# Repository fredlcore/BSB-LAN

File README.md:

# BSB-LPB-PPS-LAN

Die deutsche Fassung dieser Datei gibt es [hier](README_de.md).

Before getting started, please read through the manual [here](https://docs.bsb-lan.de).

BSB-LAN is a software/hardware solution for accessing the “Boiler-System-Bus” (BSB), the “Local-Process-Bus (LPB)” and the “Punkt-zu-Punkt-Schnittstelle” (PPS). The adapter is available for various *ESP32*-based microcontrollers (ESP32 NodeMCU, Olimex EVB, Olimex POE-ISO) as well as for an *Arduino Due* with Ethernet shield. It allows accessing the heating systems from Atlantic, Brötje, Elco and many other manufacturers via LAN/WLAN, provided that they use one of the Siemens controllers listed below. BSB-LAN makes it possible to control or regulate the heating and log any given values. This project supports almost all parameters available on the heating systems and can be used for in a comprehensive home automation environment.  

---

***Interface kits available!***  
**Interface boards are available for the ESP32 upon request. These can simply be plugged on top of one of the listed microcontrollers.Getting the board from here helps supporting this project in the future, so if you are interested, please send Frederik an e-mail (German or English) to <br /> bsb (ät) code-it.de <br /> for further information.**  

---  

Using the adapter and the BSB-LAN software, various values and parameters can easily be monitored, logged and, if so desired, controlled and changed via a web-interface.
Optional integration into existing smart home systems such as FHEM, openHAB, HomeMatic, ioBroker, Loxone, IP-Symcon, EDOMI, Home Assistant, SmartHomeNG or Node-RED is possible via MQTT, JSON or HTTP access. 
The adapter can also be used as a standalone logger without LAN or Internet connection when using a microSD card (MBR partition / FAT format).  
Temperature and humidity sensors can also be connected and their data can also be logged and analyzed. The option of integrating your own code into the BSB-LAN software also offers a wide range of expansion options. 
        
**In the following, some model series from different manufacturers are listed, which usually have installed BSB-LAN compatible controllers:**  
- Brötje: BBK, BBS, BGB, BLW (**see exceptions below!**), BMK, BMR, BOB, BSK, BSW, Eurocontrol, ISR, LogoBloc, SGB, SOB, SPK, WBC (**see exceptions below!**), WBS (**see exceptions below!**), WGB (**see exceptions below!**), WMC, WMS, WOB
- **Not working Brötje models: BOK, BLW Eco, BLW Eco.2, BLW Mono, BLW Mono.1, BLW Neo, BLW Pro.1, BLW Split, BSW Neo, WBC 22.1/28.1, WBC 14.1/22.1, WGB-K 22.1/28.1, WGB 14.1/22.1/28.1/38.1, WHB, WHC, WHS, WLC, WLS and all others with IWR controller**  
- Bösch: heat pumps with RVS controller type
- Elco: Aerotop (**not EVO LN / Mono / Mono.2 / Split / Split.2!**), Aquatop, Rendamax, Straton, Thision (**not Thision Mini!**), Thision S, Thision S Plus, Trigon S Plus
- Alarko: Aldens WM/WS
- ATAG: QR
- Atlantic: Axeo, Alféa Excellia A.I., Alféa Extensa A.I., Hynea hybrid duo gaz, Navistem, Perfinox, Varmax
- Austria Email: LWP, LWPK
- Baxi: Luna Platinum, Luna Duo, Block Kondens
- Boesch: SLS
- Bosch: Condens 3500 F, Condens 7500 FM
- Chappée: Luna, Klista
- CitrinSolar: proClima
- CTA: Optiheat
- CTC: 380 IC
- De Dietrich: IX 145
- Deville: 9942, 9981
- District heating: RVD230
- Eco: AiWA, AW, BW, DW, heatLite, Star, TBW, WW, WWi, TWW
- Ecostar: Ecodense WT-S 45
- Etna: II GWS
- EVI Heat: Combi-7
- Ferroli: HMP
- Froeling: Rendagas Plus
- Fujitsu Waterstage: Comfort, Duo, WOHA, WSHA, WSYA, WSYK, WSYP
- Gebwell: T2
- Geminox: Thrs
- General: (aka Fujitsu Waterstage) WC13F / WOC13RIYF / WGHA 100DG
- Gorenje: Aerogor Compact, Aerogor Compact EVI, Aerogor ECO Inverter 10 A, Aerogor Split AW, Aerogor Split HD, Aerogor Split HD EVI, Aquagor, Aquagor EVI, Geogor All-In-One, Terragor, Terragor EVI
- Grünenwald: Greenheat
- GS: UnoTec
- Hansa: SND
- Herz: Commotherm 5 DeLuxe
- Hotjet: One2, Wx, ZETXe, ZETXi
- Ideal Heating: Halo Air, Logic Air Heat Pump
- Interdomo: Domostar GBK 25H/SH, OBK (HC 232)
- MAN/MHG: Ecostar 200
- MHG: EcoSmart ES, EcoStar 500, EcoStar 750, ecoWP Xe, Procon E, Procon GWB, Procon HT
- Müba: Ultra Clean Eco
- Oilon: CUBE House, GT, SH, SHx
- Olymp: RegelStar 3000, SHS, WHS
- Palazzetti: Choro Sistema Calore
- Potterton: Paramount
- Robur: Comfort Controller, K18 Simplygas / Hybrigas
- Sieger: TG11
- Šildymo Technologijų Centras (ŠTC): STC9
- Sixmadun: TG11BE
- Smartheat: UI400
- SSP: Proburner
- Strebel: S-ASX
- Sunex: Nexus
- Termomax: Termo ÖV
- Thercon: Therma Silent Coax Single, THERMA Silent Coax Combi 300/500
- Thermics: Energie
- Thermital: TBox Clima TOP
- Tifell: Biofell
- Variheat: 110C
- Viadrus : Claudius K1, K2
- Viessmann: Vitotwin 300-W (exclusively!)
- Wamak: AiWa, DB
- Weishaupt: WTU  

If your heater has one of the following controllers, but your model is not listed in our manual, feel free to get in touch with us, as these models have been confirmed working:  
AVS37, AVS55, AVS71, AVS74, AVS75, AVS77, AVS79, LMS14, LMS15, LMS15, LMU64, LMU74, LMU75, RVA61, RVA63, RVA33, RVA36, RVA43, RVA46, RVA47, RVA53, RVA60, RVA61, RVA63, RVA65, RVA66, RVC32, RVD110, RVD115, RVD120, RVD125, RVD130, RVD135, RVD139, RVD140, RVD144, RVD145, RVD230, RVD235, RVD240, RVD245, RVD250, RVD255, RVD260, RVD265, RVL469, RVL470, RVL471, RVL472, RVL479, RVL480, RVL481, RVL482, RVP320, RVP330, RVP340, RVP350, RVP351, RVP360, RVP361, RVP5xx, RVS13, RVS21, RVS23, RVS26, RVS41, RVS43, RVS46, RVS47, RVS51, RVS53, RVS61, RVS63, RVS65, RVS68, RWI65, WRI80
<BR><BR>

<B>Attention!</B><BR>
Some companies which previously used BSB/LPB in their heating systems have now switched to other systems for their lower-cost devices. Examples are Brötje's WLC/WLS/BOK series. These are not compatible with BSB/LPB and only allow very limited parameters to be configured by the user. If you have one of these heating systems, you are so far out of luck to configure and monitor your heating system as it can be done with the more expensive (but BSB/LPB compatible) devices mentioned above among others.
In addition, there are now also Siemens controllers that no longer expose BSB/LPB connectors, but use different bus systems, for example the LMU34 and the Climatix/POS-series.
<BR><BR>
Instructions on how to configure etc. can be found in the <A HREF="https://docs.bsb-lan.de">manual</A>.<BR>
The forum thread that led to the development of this interface can be found <A HREF="http://forum.fhem.de/index.php?topic=29762.new;topicseen#new">here</A>.<BR>
(Forum is in German, but several members speak English)

Please take note that while the board can also be used on the Raspberry Pi, the software provided here only runs on the ESP32 and Arduino Due respectively! For using the board with the Pi, you have to use the software bsb_gateway which is available <A HREF="https://github.com/loehnertj/bsbgateway">here</A>. Please also note that the functionality differs significantly, and that you would have to contact the author of bsb_gateway for any question related to it.

Web-Interface screenshots:

BSB-Board populated for ESP32 Olimex boards:

BSB-Board on Olimex POE inside the project's 3D-printed case:

<br />This work is licensed under a <a rel="license" href="http://creativecommons.org/licenses/by-nc-sa/4.0/">Creative Commons Attribution-NonCommercial-ShareAlike 4.0 International License</a>.

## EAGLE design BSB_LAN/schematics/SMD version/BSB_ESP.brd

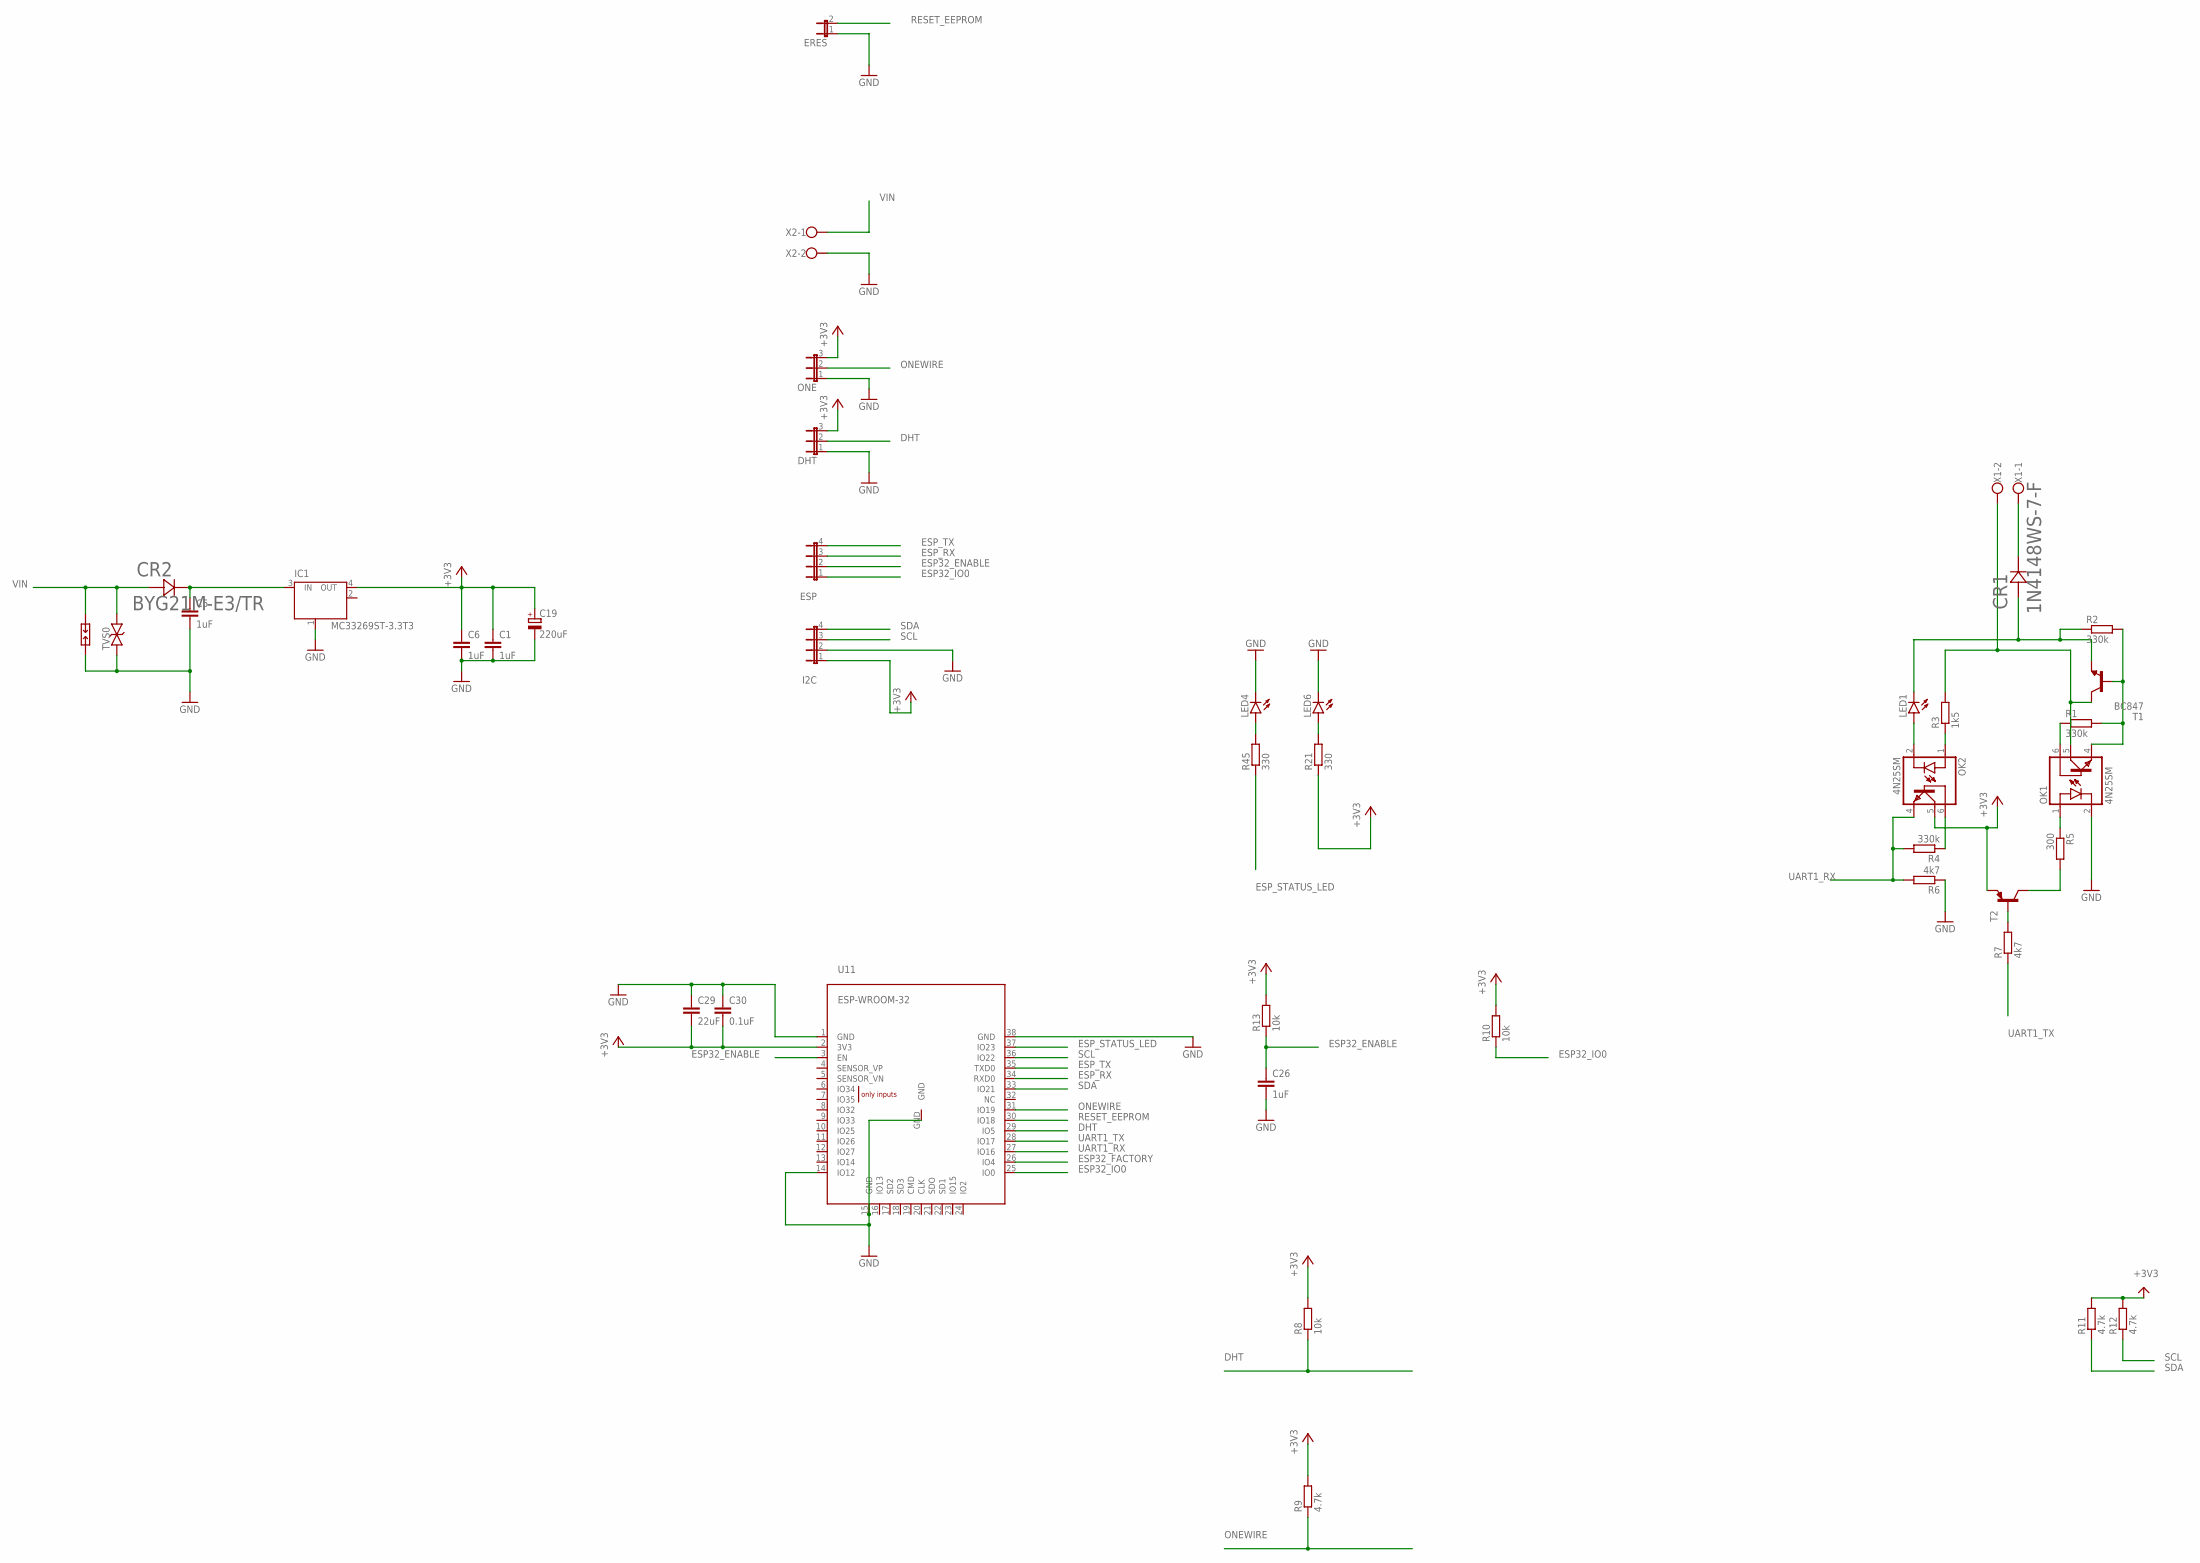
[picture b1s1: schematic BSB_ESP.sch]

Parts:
C1: 1uF; C1210
C5, C6: 1uF; C0805
C19: 220uF; 153CLV-0807
C26: 1uF; C0603
C29: 22uF; C0805
C30: 0.1uF; C0805
CR1: 1N4148WS-7-F; SOD323_DIO
CR2: BYG21M-E3/TR; DO-214AC_VIS
DHT: JP2E; JP2
ERES: JP1E; JP1
ESP: JP4E; JP4
I2C: JP4E; JP4
IC1: MC33269ST-3.3T3; SOT223
LED1, LED4, LED6: LEDCHIP-LED0805; CHIP-LED0805
OK1, OK2: 4N25SM; DIL6-SMD
ONE: JP2E; JP2
R1, R2, R4: 330k; R0603
R3: 1k5; R0603
R5: 300; R0603
R6, R7: 4k7; R0603
R8: 10k; R0402
R9: 4.7k; R0402
R10, R13: 10k; R0603
R11, R12: 4.7k; R0603
R21, R45: 330; R0603
SP0: PCB-SGAP
T1: BC847; SOT23
T2: BC857A-PNP-SOT23-BEC; SOT23-BEC
TVS0: 43CA; SMB
U11: ESP-WROOM-32
X1, X2: W237-102

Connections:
+3V3: C1.1, C6.1, C19.+, C29.2, C30.2, DHT.3, I2C.1, IC1.4 (OUT), OK2.5 (COL), ONE.3, R8.2, R9.2, R10.2, R11.2, R12.2, R13.2, R21.1, T2.E, U11.2 (3V3)
DHT: DHT.2, R8.1, U11.29 (IO5)
ESP32_ENABLE: C26.1, ESP.2, R13.1, U11.3 (EN)
ESP32_FACTORY: U11.26 (IO4)
ESP32_IO0: ESP.1, R10.1, U11.25 (IO0)
ESP_RX: ESP.3, U11.34 (RXD0)
ESP_STATUS_LED: R45.1, U11.37 (IO23)
ESP_TX: ESP.4, U11.35 (TXD0)
GND: C1.2, C5.2, C6.2, C19.-, C26.2, C29.1, C30.1, DHT.1, ERES.1, I2C.2, IC1.1 (GND/ADJ), LED4.C, LED6.C, OK1.2 (C), ONE.1, R6.1, SP0.2, TVS0.A, U11.1 (GND), U11.14 (IO12), U11.15 (GND), U11.38 (GND), U11.GND, X2.2
unnamed: CR1.1, X1.1
unnamed: OK2.1 (A), R3.1
unnamed: LED1.A, OK2.2 (C)
unnamed: OK1.5 (COL), R3.2, T1.3 (C), X1.2
unnamed: OK1.6 (BAS), R1.1
unnamed: OK1.4 (EMI), R1.2, R2.2, T1.1 (B)
unnamed: CR1.2, LED1.C, R2.1, T1.2 (E)
unnamed: OK2.6 (BAS), R4.1
unnamed: R7.2, T2.B
unnamed: OK1.1 (A), R5.1
unnamed: R5.2, T2.C
unnamed: LED4.A, R45.2
unnamed: LED6.A, R21.2
ONEWIRE: ONE.2, R9.1, U11.31 (IO19)
RESET_EEPROM: ERES.2, U11.30 (IO18)
SCL: I2C.3, R12.1, U11.36 (IO22)
SDA: I2C.4, R11.1, U11.33 (IO21)
UART1_RX: OK2.4 (EMI), R4.2, R6.2, U11.27 (IO16)
UART1_TX: R7.1, U11.28 (IO17)
VIN: CR2.2, SP0.1, TVS0.C, X2.1
VIN_POS: C5.1, CR2.1, IC1.3 (IN)

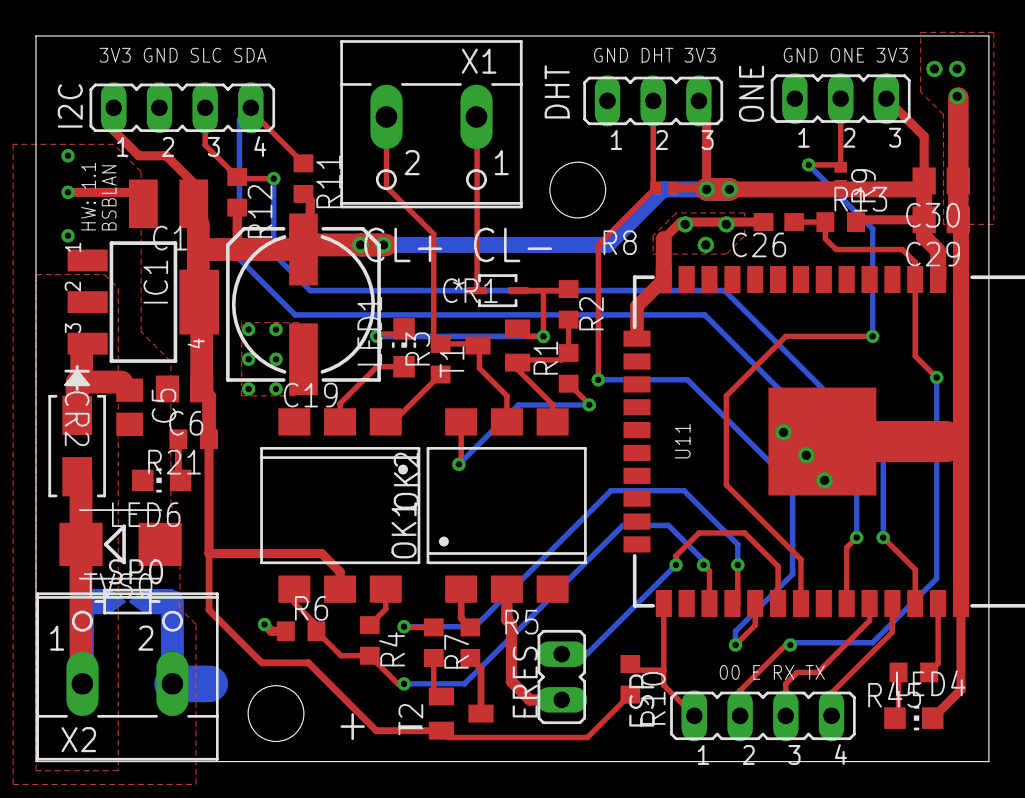
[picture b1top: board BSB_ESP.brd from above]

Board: 2 copper layers, 52.9 x 40.3 mm, 42 parts (0 on the bottom side), 29 nets.

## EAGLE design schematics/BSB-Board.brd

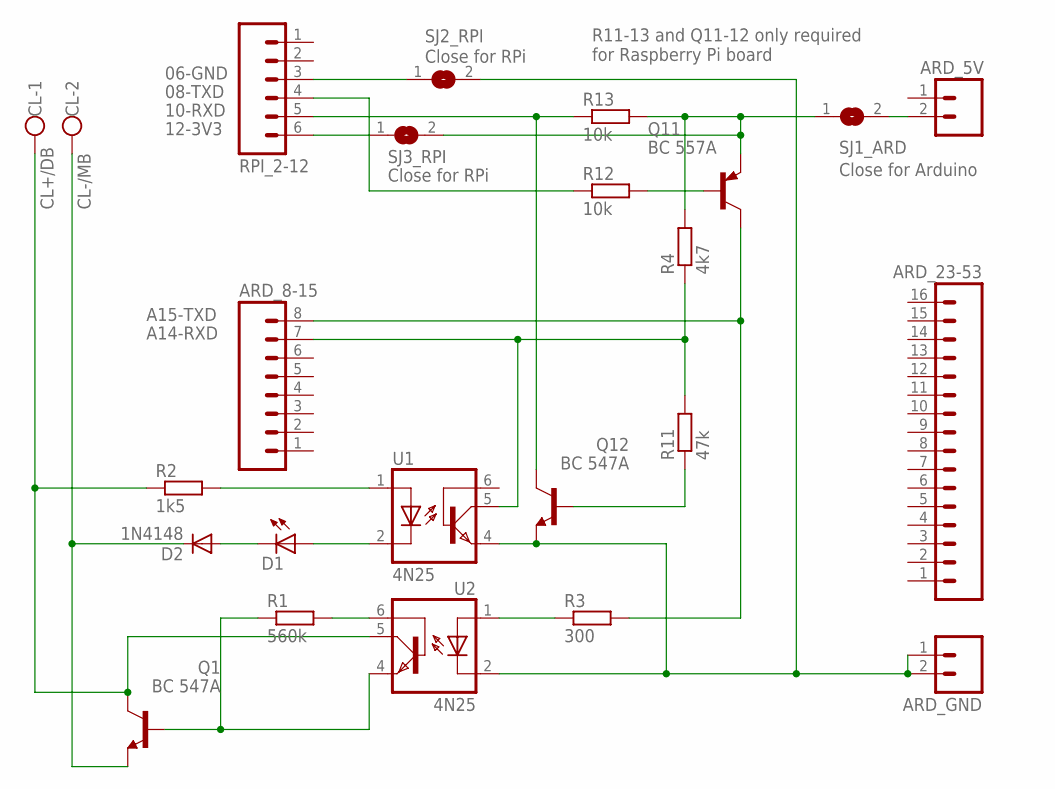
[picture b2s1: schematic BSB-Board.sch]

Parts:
ARD_5V: M02PTH; 1X02
ARD_8-15: M08; 1X08_ROUND
ARD_23-53: M16PTH; 1X16
ARD_GND: M02PTH; 1X02
CL: W237-102
D1: LEDSQR2X5; LED2X5
D2: 1N4148; DO35-7
Q1, Q12: BC 547A; TO92-CBE
Q11: BC 557A; TO92-CBE
R1: 560k; 0204/7
R2: 1k5; 0204/7
R3: 300; 0204/7
R4: 4k7; 0204/7
R11: 47k; 0204/7
R12, R13: 10k; 0204/7
RPI_2-12: M06SILK_FEMALE_PTH; 1X06
SJ1_ARD: Close for Arduino; SJ
SJ2_RPI, SJ3_RPI: Close for RPi; SJ
U1, U2: 4N25; DIL06

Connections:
5V-ARD: ARD_5V.2, SJ1_ARD.2
A14-RXD-ARD: ARD_8-15.7, R4.1, R11.2, U1.5 (COL)
A15-TXD-ARD: ARD_8-15.8, Q11.C, R3.2
ARD_PI_TXD: R3.1, U2.1 (A)
CL+: CL.1, Q1.C, R2.1, U2.5 (COL)
CL-: CL.2, D2.C, Q1.E
GND-ARD: ARD_GND.1, ARD_GND.2, Q12.E, SJ2_RPI.2, U1.4 (EMI), U2.2 (C)
GPIO14-TXD-PI: R12.1, RPI_2-12.4
GPIO15-RXD-PI: Q12.C, R13.1, RPI_2-12.5
GPIO18-3V3-PI: RPI_2-12.6, SJ3_RPI.1
unnamed: R2.2, U1.1 (A)
unnamed: D1.A, U1.2 (C)
unnamed: R1.2, U2.6 (BAS)
unnamed: D1.K (C), D2.A
unnamed: Q1.B, R1.1, U2.4 (EMI)
unnamed: Q12.B, R11.1
unnamed: Q11.B, R12.2
PIN6-GND-PI: RPI_2-12.3, SJ2_RPI.1
VCC: Q11.E, R4.2, R13.2, SJ1_ARD.1, SJ3_RPI.2

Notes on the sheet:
A15-TXD
A14-RXD
12-3V3
10-RXD
08-TXD
06-GND
CL+/DB
CL-/MB
R11-13 and Q11-12 only required for Raspberry Pi board

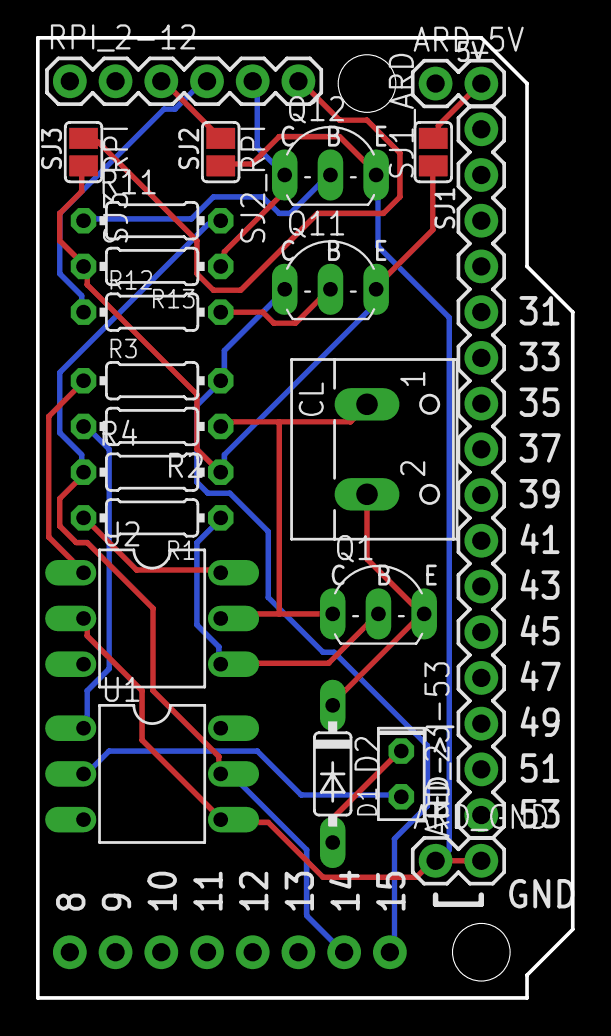
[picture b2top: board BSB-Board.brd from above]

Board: 2 copper layers, 29.7 x 53.3 mm, 23 parts (1 on the bottom side), 19 nets.

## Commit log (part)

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2025-10-01 Update COMPILETIME and optionally PATCH [automated]
2025-10-01 Remove quotes to prevent glob failure
2025-10-01 Added workflow_dispatch as trigger
2025-10-01 Fixed file name
2025-10-01 Update language resources [skip ci]
2025-10-01 Typo
2025-10-01 Avoid race conditions
2025-10-01 Added Brötje BSW Neo to the list of non-compatible systems
2025-10-05 Revert fixes
2025-10-06 Deployed 849f055e with MkDocs version: 1.6.0
2025-10-06 Added note for read-only parameters in auto-discovery
2025-10-14 Improved bugfix for Olimex powering problem, now re-enabling serial commands
2025-10-14 Remove debug messages
2025-10-14 Bugfix for DWORD fractions
2025-10-15 esp32 lib bug -> workaround for /DG, etc.
    https://github.com/espressif/arduino-esp32/issues/11908 has lead to random values in datalog.idx, breaking /DG (through the underlying /Da-b) as well as /Dn, and making /DKn outright dangerous (could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
    This commit presents a workaround - which could be removed/undone once the library has been fixed.
2025-10-16 debug message removed
    the value it provides can be found in /DI anyway
2025-10-18 Move telegram construction parts from _send to Send
2025-10-19 Remove requirement of telegram length for calling _send
2025-10-22 Revert "Fix critical buffer overflow vulnerability in HTTP request parsing"
    This reverts commit d103258c4c7fc5775ac712d8bfa39858b6bff61c.
2025-10-27 Added data type VT_BYTE2
2025-10-27 Added data type VT_BYTE2, bugfix for debug output for non-Olimex devices
2025-10-27 Bugfix for broadcast
2025-10-27 Added /YR command to send raw data to the bus
2025-10-28 Updated relay command /YR
2025-10-28 Code snippet to use OCI700 on a remote heating system using two BSB-LAN devices
2025-11-01 Critical bug fix for PPS for a bug introduced a few weeks ago. Add function to temporarily set new bus destination
2025-11-01 Take care of QINF telegrams
2025-11-01 Take care of (or rather ignore) 0x2D messages on RVD controllers.
2025-11-02 Added Variheat 110C as compatible heater
2025-11-02 Add preliminary IPv6 support
2025-11-05 Removed IPv6 support due to issues reported by users
2025-11-05 Exclude Ethernet.macAddress(mac) for Arduino Due
2025-11-10 Added issues with some Atlantic heaters that do not sync their display with the Siemens controller
2025-11-10 Deployed 7b1ba3db with MkDocs version: 1.6.0
2025-11-10 Added value type VT_MINUTES_N
2025-11-11 simple dark mode
    ...for muted white on black HTML pages
    must be explicitely enabled in *config.h
2025-11-13 Added value types VT_UINT_HALF and VT_TEMP_PER_HOUR
2025-11-13 Moved 3D printer files to dedicated folder
2025-11-14 Example code for handling error broadcast messages
2025-11-14 Moved example to custom_functions
2025-11-14 Added details for 10189 and 10199
2025-11-14 Send valid values even for disabled parameters. Code clean-up.
2025-11-14 Warning of potential wrong use of VT_HOURS_WORD (parameter 7040)
2025-11-14 Adjust debug output
2025-11-24 Update Home Assistant integration details
    Clarified the integration works again.
2025-11-24 Updated list of controllers
2025-11-24 Bugfix for temporary AP
2025-12-02 Added more ENUM_ONOFFs
2025-12-02 Spelling error
2025-12-02 Updated ChangeLog
2025-12-04 Added exceptions and clarifications for supported controllers
2025-12-07 Added incompatible heaters
2025-12-08 Bugfix for device specific parameter list generation
2025-12-08 Custom function for enabling IPv6
2025-12-08 Added descriptions for recently added custom functions
2025-12-08 Added incompatible heating systems
2025-12-26 Deployed 21de1927 with MkDocs version: 1.6.0
2025-12-28 Remove compiler warning
2025-12-28 Bugfix for https://github.com/fredlcore/BSB-LAN/issues/783
2025-12-30 Update flat connector links to fully insulated version
2026-01-08 Deployed 8455ec0f with MkDocs version: 1.6.1
2026-01-08 Added Google Home integration
2026-01-11 Bugfix for PPS burner status parameter
2026-01-19 Added translation for error priority text
2026-01-19 Added testimonials
2026-01-19 Added missing anchors
2026-01-19 Removed warnings
2026-01-19 Removed URL checking since almost all letters are allowed anyway
2026-01-19 Added error priority
2026-01-19 In case of an error, send "---" as parameter value to MQTT broker instead of not sending anything at all.
2026-01-20 Update ChangeLog
2026-01-23 Added priority field in debug message.
2026-01-24 Deployed cf968b2e with MkDocs version: 1.6.1
2026-01-25 Added requested language information
2026-01-25 Added reminder to enable OTA before using it.
2026-01-25 Deployed 70385935 with MkDocs version: 1.6.1
2026-01-26 Updated Home Assistant information
2026-01-26 Deployed 90a70b88 with MkDocs version: 1.6.1
2026-01-28 Added troubleshooting tips for Arduino IDE timeouts
2026-01-30 Update testimonials
2026-01-31 Added TLS functionality, used for example to connect to remote MQTT brokers. Disable with NO_TLS definement.
2026-01-31 Deployed d37cd251 with MkDocs version: 1.6.1
2026-01-31 Reminder to write bug reports in English
2026-01-31 Disable TLS on Arduino Due
2026-01-31 Removed unnecessary condition as TLS is only available on ESP32 anyways
2026-01-31 Added breaking changes due to TLS
2026-01-31 Check for valid certificate
2026-02-07 Added connection instructions
2026-02-07 Added CUSTOM_PARTITION_TABLE definement for microcontrollers with more than 4MB flash
2026-02-08 Updated library and added session state check
2026-02-08 Added instructions on how to call hosts with self-signed certs
2026-02-08 Added MQTT and TLS/SSL related changes
2026-02-08 Allow disabling for cert checking if you really know what you're doing
2026-02-09 Added full name for Ideal Heating Logic Air heat pumps
2026-02-09 Updated testimonials
2026-02-11 Deployed 11eb108b with MkDocs version: 1.6.1
2026-02-11 Added automatic update of MQTT auto-discovery in case broker lost session state
2026-02-11 Moved partition check after including BSB_LAN_config.h
2026-02-21 Added check in case Arduino IDE moved BSB_LAN.ino to new sub-folder
2026-02-21 Deployed c4f35fbd with MkDocs version: 1.6.1
2026-02-26 github actions artefakte für web flash
2026-02-26 remove arduino duo
2026-02-26 readme web flash
2026-02-26 add readme web flash
2026-02-26 Split compile steps to Arduino end ESP32, create recovery firmware
2026-02-26 Rename file
2026-02-26 Deployed b0106043 with MkDocs version: 1.6.1
2026-02-26 Update workflow
2026-02-26 Updated workflows
2026-02-26 Guard __has_include on Arduino Due
2026-02-26 Fix type
2026-02-26 Bugfix
2026-02-26 Wrong indention
2026-02-26 More bugfixes
2026-02-26 Added web recovery flasher (Chrome/Edge) with minimal working firmwares
2026-02-27 Rename files
2026-02-27 Bugfixes
2026-02-27 Rename docs/EN to docs/en
2026-02-27 Change default language to English for default minimal recovery firmware
2026-02-27 Recovery flasher added
2026-02-27 Remove outdated files
2026-02-27 Streamlining build process
2026-02-27 Added 16MB partition
2026-02-27 Adjust manifest filenames
2026-02-27 Remove find commands, use hard-coded locations instead
2026-02-27 Enable custom partition table for POE-ISO-16MB
2026-03-02 Update pubsubclient to pubsubclient3 by hmueller (https://github.com/hmueller01/pubsubclient3 | https://www.arduinolibraries.info/libraries/pub-sub-client3)
2026-03-02 Add sessionPresent functionality (needs a PR on the upstream version)
2026-03-03 Use QoS 1 for publishing MQTT topics
2026-03-03 Transmit actual IP address to broker
2026-03-04 Clarification of UseEEPROM
2026-03-07 Added information on SD card partition/formatting details
2026-03-12 Fixed typos
2026-03-13 Set size of logo in UI rather than 10% of window width
2026-03-14 Clamp logo size to allow reasonable scaling range
2026-03-15 Add GPIO input pull-up mode via /Gx,IP
2026-03-15 remove function, logic inline
2026-03-15 Added info that PPS has no device-specific parameter lists
2026-03-15 Added /Gxx,IP to activate pull-up for GPIO xx
2026-03-16 Release version 5.1
2026-03-24 Prevent stale outBufLen
2026-03-26 Bugfix preventing crash during parameter file download
2026-04-22 Added parameter to enable bus power supply and LPBKonfig0
2026-04-24 Correction on when TLS is used when connecting to MQTT brokers
2026-04-25 Added Interdomo OBK with HC 232 controller (RVS63)
2026-05-05 Handle missing CONFIG_FREERTOS_NUMBER_OF_CORES define
    When building with platformio, this define does not appear to exist.
    Based on an example on the Arduino community forum, they use `configNUM_CORES` for this purpose, which the Arduino ESP32 libs define as 2 (same as original value before this define was used).
    Add a failback define in case the former is not defined.
2026-05-08 fix(mqtt): Fix stack-buffer overflow in mqtt_callback
2026-05-08 fix(vacationmode): Fix vacation mode for Siemens RVS21
2026-05-12 Refactor BSSID connection logic in scanAndConnect function
    When defining a fixed bssid to safeguard connection with a specific AP I encountered frequent dis- and reconnects with an approx ~ 1 Minute pattern. This fix changes the logic to not call WiFi.begin(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
2026-05-12 Refactor WiFi connection logic and improve scanning / connecting to strongest AP
    Enhanced scanAndConnectToStrongestNetwork() to only trigger scans if signal is weaker < -80 and encapsulate full logic to connect to strongest AP.
    Removed unnecessary "Wifi.Begin()" from Setup as this tends to stick with the last known AP and reyling on scanAndConnectToStrongestNetwork() to do the right setup
2026-05-14 Added missing return that caused ignoring selected BSSID, thanks to @schlaubstar
2026-05-19 Bugfix: BSB-LAN failed to reconnect in case of complete loss of WiFi connectivity, hopefully explaining cases where BSB-LAN is still running but without network access.
2026-05-23 Clarification
2026-05-23 Warning of incompatibility of Siemens Climatix/POS series
2026-06-08 New LMS14/15 controller photo added
2026-06-10 Updated root certs

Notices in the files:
parts and their libraries:
COPYRIGHT: Copyright (C) 2021 Ultra Librarian. All rights reserved.
SparkFun-Connectors: Licensing: Creative Commons ShareAlike 4.0 International - https://creativecommons.org/licenses/by-sa/4.0
